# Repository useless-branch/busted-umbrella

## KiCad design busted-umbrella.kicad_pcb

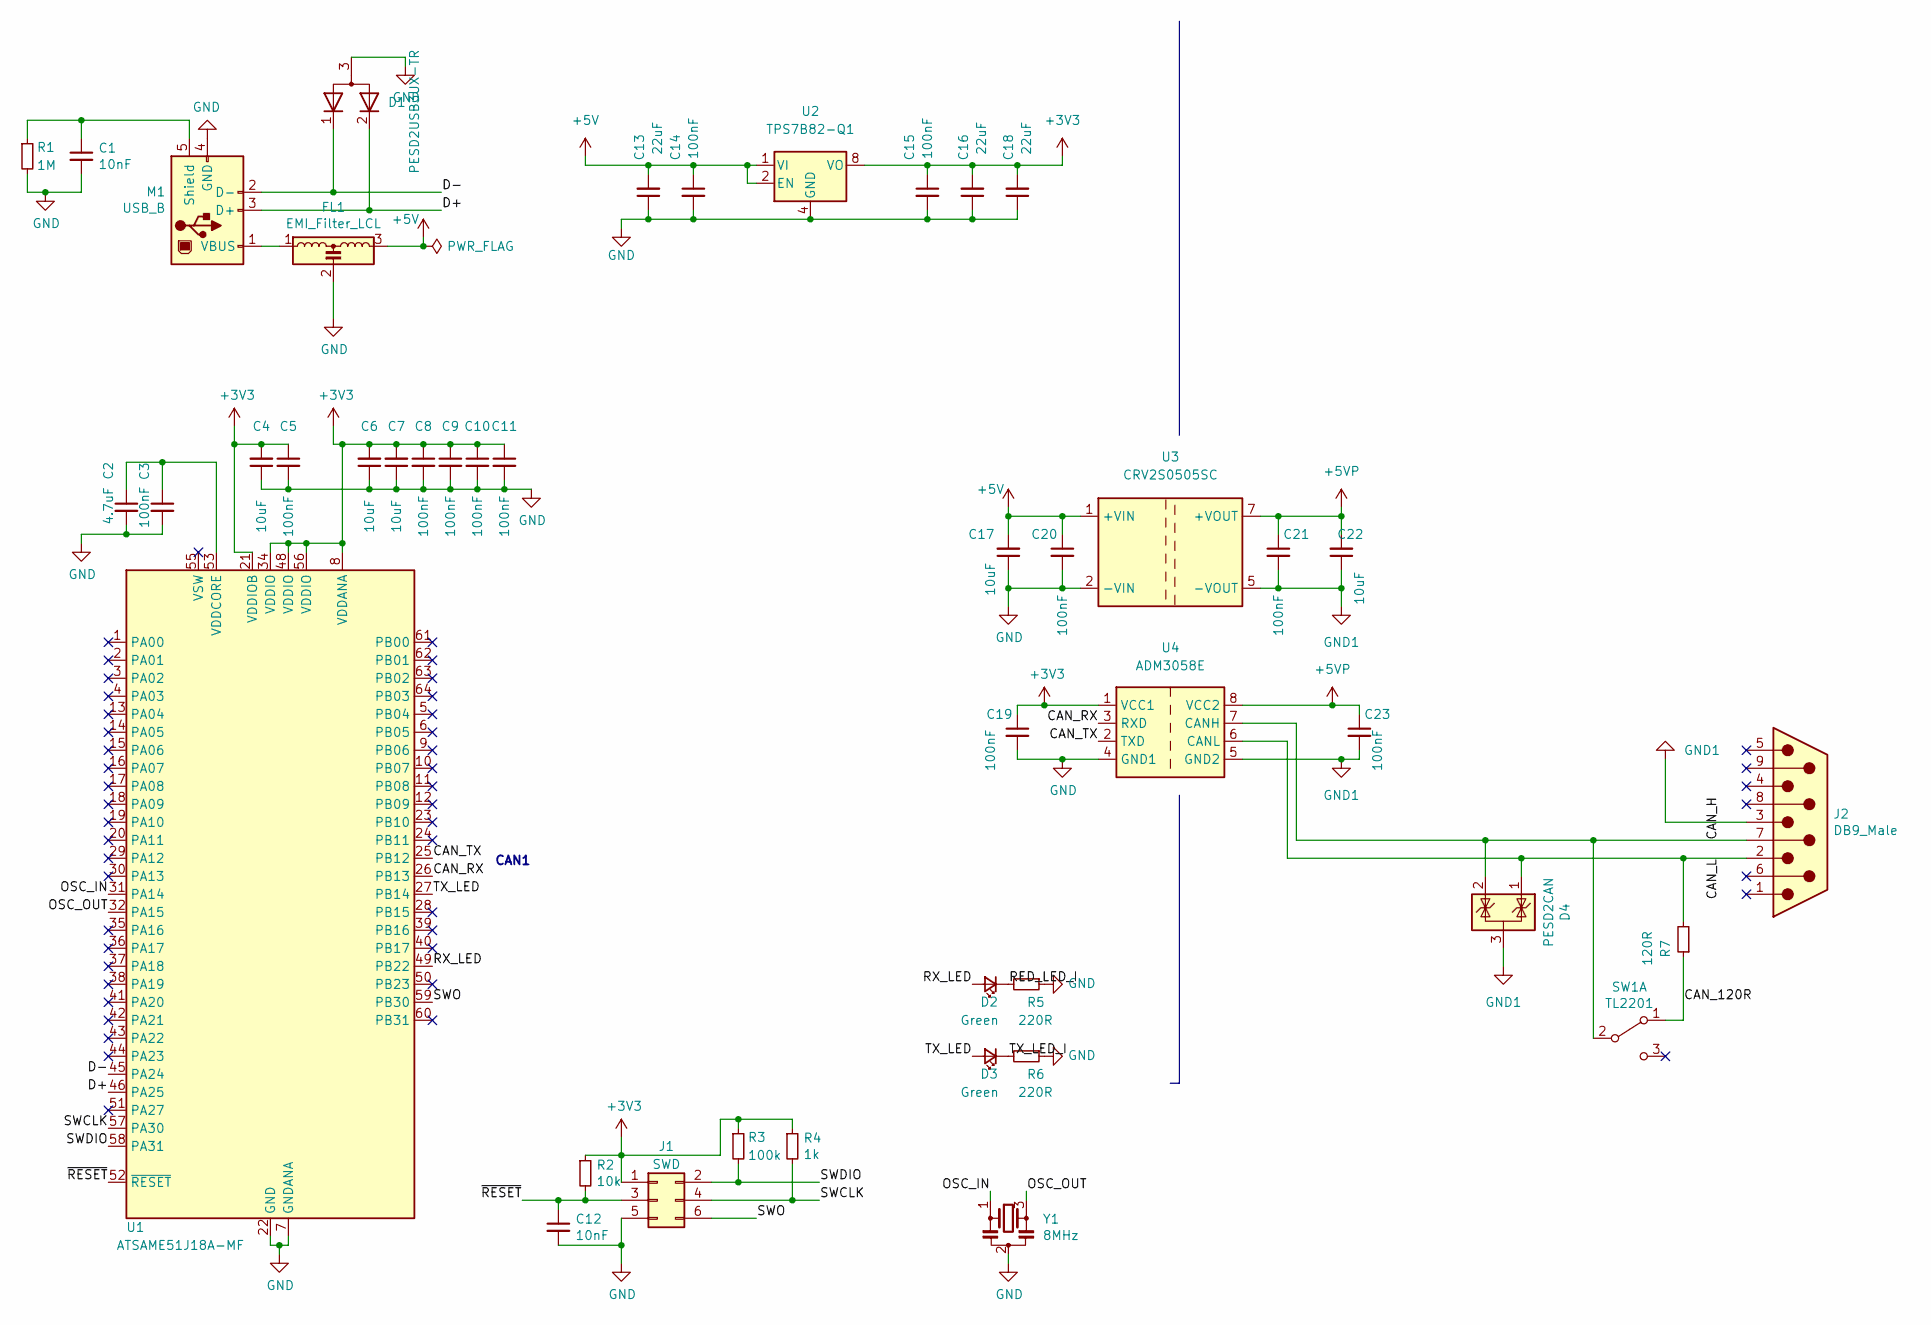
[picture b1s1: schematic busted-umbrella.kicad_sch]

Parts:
C1, C12: 10nF; C_0402_1005Metric; MOUSER_NO 81-GRM155R71H103JA8D
C2: 4.7uF; C_0603_1608Metric; MOUSER_NO 81-GRM188C71A475KE1D
C3, C5, C8, C9, C10, C11, C14, C15, C19, C20, C21, C23: 100nF; C_0402_1005Metric; MOUSER_NO 81-GRM155R71H104KE4D
C4, C6, C7, C17, C22: 10uF; C_0603_1608Metric; MOUSER_NO 81-GRM188D71A106MA3D
C13, C16, C18: 22uF; C_0603_1608Metric; MOUSER_NO 81-GRM188C80J226ME5D
D1: PESD2USB3UX-TR; SOT-23; MOUSER_NO 771-PESD2USB3UX-TR
D2, D3: Green; LED_D3.0mm_Horizontal_O6.35mm_Z6.0mm; MOUSER_NO 604-WP710A10LGD
D4: PESD2CAN; SOT-323_SC-70; MOUSER_NO 771-PESD2CANFD24L-UX
FL1: EMI_Filter_LCL; 3Pole_F1206; MOUSER_NO 81-NFE31PT222Z1E9L
J1: SWD; Tag-Connect_TC2030-IDC-NL_2x03_P1.27mm_Vertical; MOUSER_NO 798-DF11-6DP-2DSA01
J2: DB9_Male; DSUB-9_Male_Horizontal_P2.77x2.54mm_EdgePinOffset9.40mm; MOUSER_NO 649-DE09P564CTXLF
M1: USB_B; USB_B_OST_USB-B1HSxx_Horizontal; MOUSER_NO 538-67068-8110
R1: 1M; R_0402_1005Metric; MOUSER_NO 71-RCS04021M00JNED
R2: 10k; R_0402_1005Metric; MOUSER_NO 71-CRCW0402-10K-E3
R3: 100k; R_0402_1005Metric; MOUSER_NO 71-CRCW0402-100K-E3
R4: 1k; R_0402_1005Metric; MOUSER_NO 71-CRCW0402-1.0K-E3
R5, R6: 220R; R_0603_1608Metric; MOUSER_NO 667-ERJ-3EKF2200V
R7: 120R; R_0805_2012Metric; MOUSER_NO 667-ERJ-P06J121V
SW1: TL2201; MOUSER_NO 612-TL2201EEZA1RBLK
U1: ATSAME51J18A-MF; VQFN-64-1EP_9x9mm_P0.5mm_EP5.4x5.4mm; MOUSER_NO 556-ATSAME51J18A-MF
U2: TPS7B82-Q1; Texas_R-PDSO-G8_EP2.95x4.9mm_Mask2.4x3.1mm
U3: CRV2S0505SC; Murata_CRV2; MOUSER_NO 580-CRV2S0505SC
U4: ADM3058E; SOIC-8_7.5x5.85mm_P1.27mm; MOUSER_NO 584-ADM3058EBRIZ-RL
Y1: 8MHz; Resonator_SMD_Murata_CSTxExxV-3Pin_3.0x1.1mm; MOUSER_NO 81-CSTNE8M00GH5C000R

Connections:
+3V3: C4.2, C5.1, C6.2, C7.2, C8.1, C9.1, C10.1, C11.1, C15.1, C16.2, C18.2, C19.1, J1.1, R2.1, R3.1, R4.1, U1.8 (VDDANA), U1.21 (VDDIOB), U1.34 (VDDIO), U1.48 (VDDIO), U1.56 (VDDIO), U2.8 (VO), U4.1 (VCC1)
+5V: C13.2, C14.1, C17.2, C20.1, FL1.3, U2.1 (VI), U2.2 (EN), U3.1 (+VIN)
+5VP: C21.1, C22.2, C23.1, U3.7 (+VOUT), U4.8 (VCC2)
/CAN_120R: R7.1, SW1.1 (A)
/CAN_H: D4.2 (K), J2.7, SW1.2 (B), U4.7 (CANH)
/CAN_L: D4.1 (K), J2.2, R7.2, U4.6 (CANL)
/CAN_RX: U1.26 (PB13), U4.3 (RXD)
/CAN_TX: U1.25 (PB12), U4.2 (TXD)
/D+: D1.2 (K), M1.3 (D+), U1.46 (PA25)
/D-: D1.1 (K), M1.2 (D-), U1.45 (PA24)
/OSC_IN: U1.31 (PA14), Y1.1
/OSC_OUT: U1.32 (PA15), Y1.3
/RED_LED_I: D2.1 (K), R5.2
/RX_LED: D2.2 (A), U1.49 (PB22)
/SWCLK: J1.4, R4.2, U1.57 (PA30)
/SWDIO: J1.2, R3.2, U1.58 (PA31)
/SWO: J1.6, U1.59 (PB30)
/TX_LED: D3.2 (A), U1.27 (PB14)
/TX_LED_I: D3.1 (K), R6.2
/~RESET: C12.1, J1.3, R2.2, U1.52 (~RESET)
GND: C1.2, C2.2, C3.2, C4.1, C5.2, C6.1, C7.1, C8.2, C9.2, C10.2, C11.2, C12.2, C13.1, C14.2, C15.2, C16.1, C17.1, C18.1, C19.2, C20.2, D1.3 (A), FL1.2, J1.5, M1.4 (GND), R1.2, R5.1, R6.1, U1.7 (GNDANA), U1.22 (GND), U1.33 (GND), U1.47 (GND), U1.54 (GND), U2.3 (GND), U2.4 (GND), U2.5 (GND), U2.6 (GND), U2.7 (GND), U2.9 (GND), U3.2 (-VIN), U4.4 (GND1), Y1.2
GND1: C21.2, C22.1, C23.2, D4.3 (A), J2.3, U3.5 (-VOUT), U4.5 (GND2)
unnamed: C1.1, M1.5 (Shield), R1.1
unnamed: C2.1, C3.1, U1.53 (VDDCORE)
unnamed: FL1.1, M1.1 (VBUS)

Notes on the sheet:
CAN1

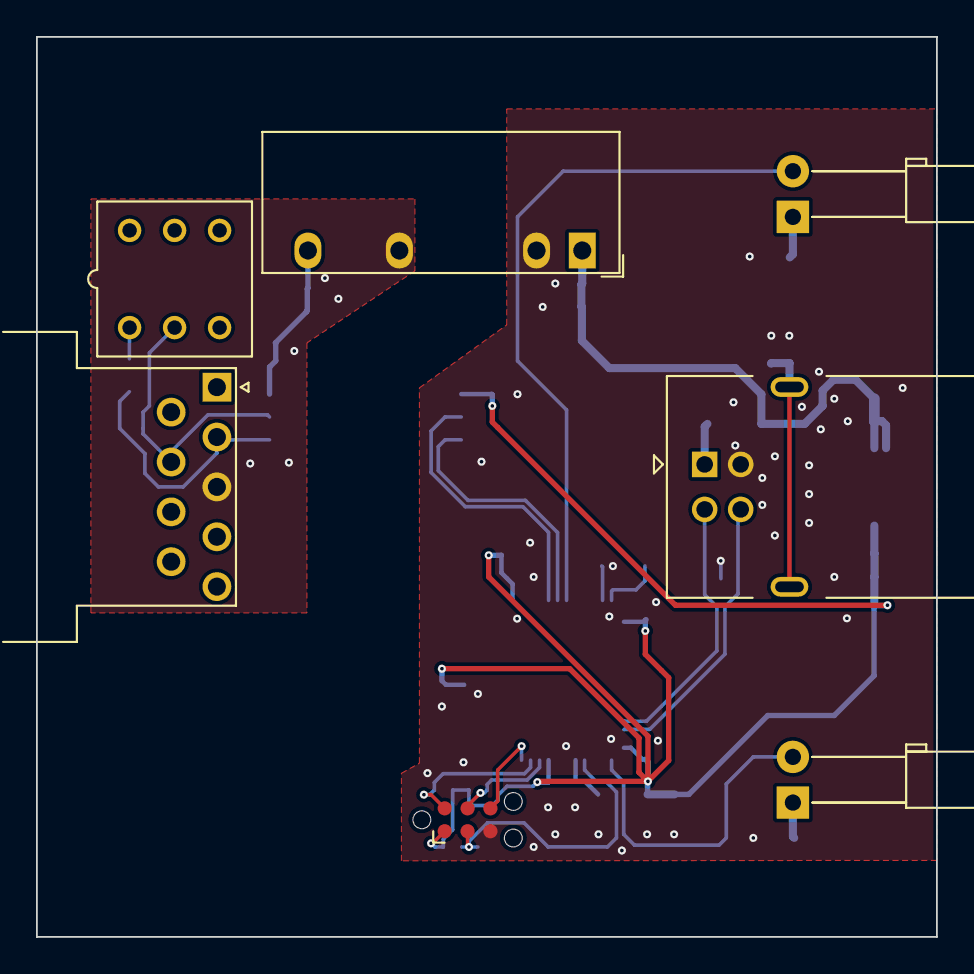
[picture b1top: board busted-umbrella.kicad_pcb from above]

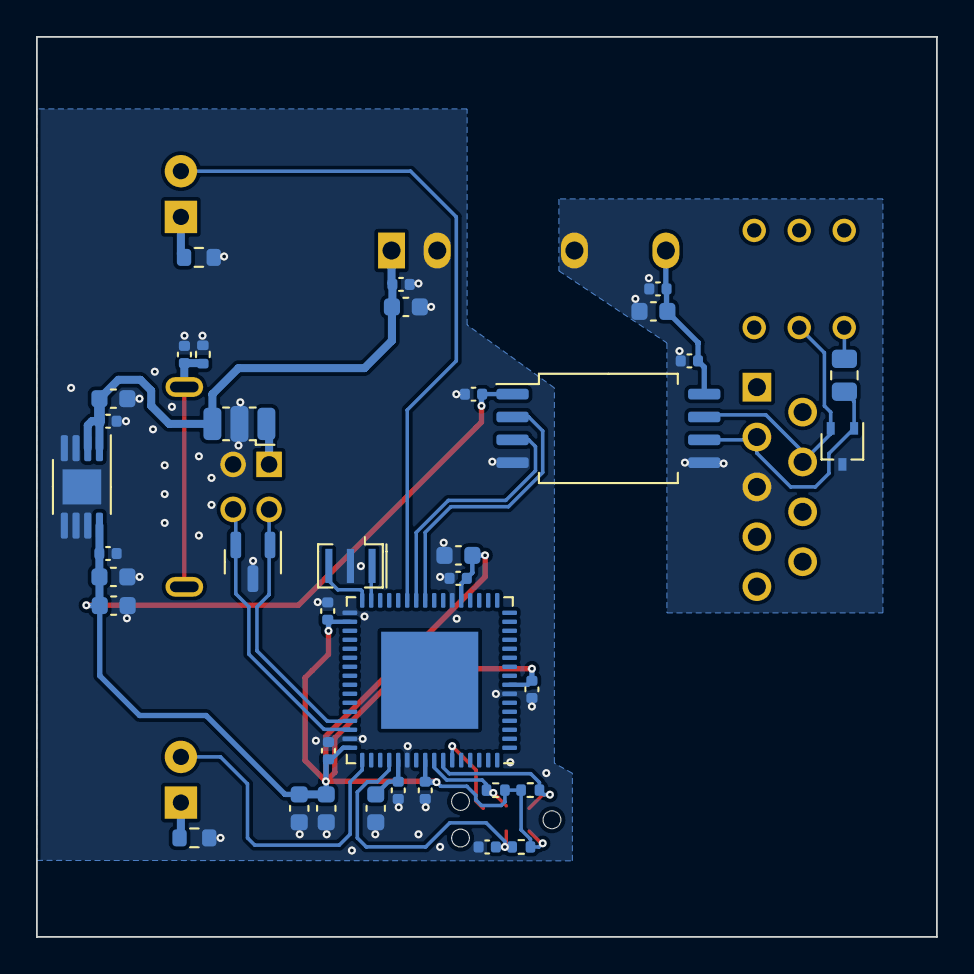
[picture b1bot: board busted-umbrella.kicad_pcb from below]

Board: 4 copper layers, 50.0 x 50.0 mm, 44 parts (37 on the bottom side), 25 nets.

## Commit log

2021-11-19 schematic and layout finished (maybe)
2021-12-01 changed ldo
2022-02-27 updated project
